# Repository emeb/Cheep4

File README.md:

# Cheep4

Yet another Eurorack digital oscillator

## Abstract

Cheep4 is a continuation of a series of low-spec / low-cost digital oscillator modules for Eurorack whose primary purpose is to demonstrate using extreme low-end microcontrollers to do DSP. The series includes the following earlier modules:

[cheep_mod](https://github.com/emeb/Old_Website/tree/main/synth/cheep_mod) - the original stripped-down done with an STM32F030 and a SPI DAC.

[cheep2](https://github.com/emeb/Old_Website/tree/main/synth/cheep2) - 2nd generation uses an STM32F031 and a stereo I2S DAC.

[cheep3a](https://github.com/emeb/cheep3a) - 3rd generation based on a CH32V003 and stereo I2S DAC faked out with a SPI interface.

Cheep4 dials up the functionality with a more advanced MCU - the STM32C542CCT6 which although more powerful is still inexpensive (under $2) - and a decent quality I2S DAC, as well as a more complete set of controls for the 1V/Octave input (Coarse, Fine, FM pots). Similar to the cheep3a, it has a button & LED mode select interface which provides seven distinct algorithms and nonvolatile memory to save the mode across power cycles. Behind the panel there are also USB and Qwiic connectors for upgrades and expansion.

## Features

- [STM32C542CC](https://www.st.com/en/microcontrollers-microprocessors/stm32c542cc.html) MCU with
  
  - Arm Cortex M33 at 144MHz
  
  - 256kB Flash
  
  - 64kB SRAM
  
  - CORDIC math coprocessor

- [PCM5100A](https://www.ti.com/product/PCM5100A) I2S DAC

- [GD25Q32](https://www.gigadevice.com/product/flash/spi-nor-flash/gd25q32c)  4MB SPI flash memory

- USB port

- [Qwiic](https://www.sparkfun.com/qwiic) I2C port

- 16-pin shrouded Eurorack power connector with +/-12V only

- 6x 9mm potentiometers
  
  - Coarse pitch
  
  - Fine pitch
  
  - FM pitch attenuator
  
  - CV1, CV2, CV3 offsets

- 8x 3.5mm mono jacks
  
  - 1V/Oct pitch input (+/-5V range)
  
  - FM pitch input
  
  - CV1, CV2, CV3 inputs (+/-5V range)
  
  - Sync input (digital, 0.7V threshold)
  
  - 2 +/-5V outputs

- Button + RGB LED for mode selection.

## Firmware

Firmware included with this project includes test code for all the critical MCU features as well as functional oscillator applications. All code is built with my own simplified make-based system and needs only an Arm GCC compiler and an ST-Link programmer. Code is based on the ST HAL2 hardware interface library as well as the Arm CMSIS low-level drivers and register definitions, both of which are included in this repository.

### Prerequisites

- [Arm GCC compiler](https://developer.arm.com/downloads/-/arm-gnu-toolchain-downloads)

- [ST-Link programmer](https://www.st.com/en/development-tools/hardware-debugger-and-programmer-tools-for-stm32/products.html) hardware interface - currently the only low-cost programmer/debugger that interfaces to the STM32C5 family MCUs.

- [STM32 Cube Programmer]([https://www.st.com/en/development-tools/stm32cubeprog.html) application installed - needed for interfacing to ST-Link programmer hardware. 

### Building

Change directories into the desired subdirectory and run `make` - this may require editing the Makefile to point to the installation locations of you prerequisites.

## Hardware

Kicad 9.0.x design files are included for both the passive front panel and active back panel. A Libreoffice ODS spreadsheet of the Bill of Materials (BOM) is available, or you can generate your own desired format from Kicad. No special assembly techniques are required beyond basic SMT and thru-hole soldering. Documentation includes:

- [Schematic (PDF format)](./doc/cheep4_sch.pdf)

- [Bill of Materials (ODS format)](Hardware/cheep4/cheep4_bom.ods)

## Lessons Learned

This project involved a fair bit of new material for me - not only is the STM32C542 a new family of MCU, but ST has chosen to migrate to a new HAL2 API for interfacing to their hardware, as well as a newer CubeMX2 configuration & code generation application. What follows are some notes on the new hardware, firmware and software experiences.

### STM32C542CCT6 Microcontroller

This device is a new low-cost part with a decent complement of peripherals and memory. The specific part chosen here is in a 48-pin LQFP which is just enough for all the interfaces needed on this oscillator project, including some diagnostic test pads, but there are larger (and smaller) pincount packages available. Overall the device doesn't feel significantly different from earlier offerings from STM, but there are some slight differences worth calling out:

##### Cortex M33 CPU

This type of CPU has been appearing in more and more devices lately, edging out the older Cortex M3, M4 and M7 cores that were common in the STM32 line. The main difference is support for secure boot which is critical for some applications but of no great interest to me.

##### Clock Generation

In the past most STM32 microcontrollers were outfitted with crystal oscillators, RC oscillators and PLLs that could synthesize a wide range of system clock frequencies from these sources. The STM32C5 family still supports crystal and RC oscillators but replaces the older more flexible PLLs with new "Programmable Speed Internal" sources which appear to be phase-locked oscillators with a very limited selection of reference and output frequencies. They still provide accurate and clean clock signals when properly configured, but cannot support fine resolution in selection of system clocks and generate only 100, 144 and 160MHz outputs (and some integer divisions of these).

##### EEPROM Emulation

The C5 family includes a new "User Data" region of flash memory which is addressed and managed separately from the typical program flash that's been a staple of previous STM32 parts. The User Data region has smaller sector sizes, more error correction bits and finer granularity when writing which allows more effective implementation of EEPROM data storage.

##### CORDIC coprocessor

First introduced in the STM32G4 series parts, this function allows fast and accurate computation of trigonometric and hyperbolic math functions without use of the main CPU. It's a very handy thing to have when doing DSP and audio applications and a welcome feature in a low-end "value" device.

##### Common Peripherals

The C5 family also has the usual assortment of SPI, I2C, I2S, CAN, UART, ADC, DAC and other peripherals. For the most part they are very similar to the same functions in earlier STM32 parts with minor variations as are typical across families.

##### Board design

At the package pin interface the C5 parts will be very familiar to anyone who has designed with earlier STM32 parts. The pin arrangements follow the same general layout and electrical characteristics are also similar. A few notable differences are:

- The use of the BOOT0 pin which is A) disabled by default in the option bytes and must be explicitly enabled if the system bootloader is needed, and B) can now be repurposed as GPIO.

- There is no longer a separate VDDA supply pin for the analog subsection. There are however still Vref pins which should be driven with clean reference supplies for the ADC and DAC.

### STM32 CubeMX2 & HAL2

Alongside the C5 family of parts, ST has introduced a new configuration and code generation tool CubeMX2 and the associated HAL2 library of low-level and mid-level drivers.

###### CubeMX2

[STM32 CubeMX](https://community.st.com/t5/developer-news/introducing-stm32cubemx2-a-new-flavor-of-stm32cubemx-tool/ba-p/885793) is the hardware configuration tool that ST has provided for many years which is an essential part of bringing up a new hardware design because it helps accelerate the setup of all the hardware resources on STM32 parts. CubeMX2 fills the exact same role for the C5 family. It has a significantly different UI from the older CubeMX application but the changes aren't particularly confusing - if you know how to drive CubeMX then it won't take too much effort to learn CubeMX2. The main difference is in the structure of the generated code. CubeMX2 has a radically different project architecture, with initialization code for every MCU subsystem broken out into separate files that are hierarchically separate from the user application code.

##### HAL2

The original HAL (Hardware Abstraction Library) was the follow up to ST's earlier Standard Peripheral Library, both of which encapsulated the necessary driver code for initializing and using the peripherals on every STM32 MCU. [HAL2](https://dev.st.com/stm32cube-docs/embedded-software/2.0.0/en/architecture/hal2-architecture.html) is similar to HAL and provides most of the same resources, but is sufficiently different in details that code written for HAL on older devices will not port without some effort - many of the function calls have changed in name and parameters so some careful study of the HAL2 source will be needed to ensure that ported code operates as required. 

There are some significant improvements in HAL2 however - primarily in build-time settings to optimize resource usage. Every peripheral subsystem can be configured to enable or disable features such as assertion, debuggin, DMA, etc. as required in the target application. HAL2 seems to produce tighter firmware and the API enables fairly straightforward user code that appears sturcturally simple and is fairly easy to optimize.

### Cheep4 Application

In the specific application to a low-cost Eurorack digital oscillator, the STM32C542 features were used as follows:

##### Clocking

By default at startup the STM32C542 runs at full speed from the 144MHz HSI RC oscillator. This source is not highly accurate and exhibits a fair amount of phase noise as shown in the figure below:

After bootup, a 24MHz HSE crystal is used as reference to the PSIS generating a very clean and accurate 144MHz system clock as seen in this screenshot:

##### ADC for CV input

The C542 ADC performed very well for control voltage conversions. Driver code was based on the init code generated by CubeMX2, combined with calibration and startup functions inferred by reading examples and the documentation in the HAL2 driver. Converted data appears to be extremely clean and stable, with very little noise in the least-significant bits.

##### I2S for audio output

The C542 includes two SPI ports that also support full-duplex I2S for audio applications. Port SPI2 is configured to drive the PCM5100A audio DAC via TX-only I2S with 16-bit stereo output at a sample rate of 95744Hz - the closest rate to 96kHz available using the on-chip clocking resources. Initialization and operation via the HAL2 API was straightforward and optimization via bypassing the ISR callbacks provided a modest reduction in CPU resources used.

##### DAC for audio output

Although the Cheep4 board doesn't explicitly support use of the C542 on-chip DACs for its audio output channels, the DAC outputs are available on testpoints and could conceivably be wired into the output buffer with appropriate gain and offset changes. Driver code for the DACs has been evaluated and appears to work as expected, achieving the same stereo @ 95744Hz sample rate as was used in the I2S case. The configuration requires using one of the available timer peripherals to generate a sample-rate trigger signal to the two DAC channels, coupled to DMA driving the dual left-justified data register with 32-bit words containing two 16-bit signed data samples.

##### SPI for external flash

An external GD25Q32 4MB SPI flash chip is interfaced via port SPI1 for storage of audio samples or wavetables. XIP or memory mapped access is not available so reading and writing is handled exclusively via indirect mode. Althought this flash device supports SPI clocks in excess of 80MHz, most reliable operation was seen with a SPI prescaler of 4 yielding a clock rate of 36MHz.

##### Timer input capture for sync

A common feature found in audio oscillators is "sync" which allows resetting the phase of the oscillator to a known point to synchronize it to an external source. The Cheep4 system generates 4 stereo samples per DMA IRQ buffer period and checking for sync once per period would result in poor timing resolution that contributes to harsh aliasing distortion. By sampling the sync input with a timer at the sample rate it's possible to improve the timing resolution and reduce the aliasing distortion significantly. Timer 12 clocked at 4x the sample rate with falling-edge input capture provides a high-resolution indicator of exactly which buffer sample to apply the phase reset.

##### Button and LED user interface

An RGB LED can provide up to seven unique colors without requiring PWM for fine color resolution which would introduce supply current spikes that could contaminate the audio outputs. A single front-panel tactile pushbutton is sampled at the 1ms Systick rate, debounced and the rising edge is used to advance the LED color and audio mode. In addition to the front-panel button, the BOOT0 button on the back of the PCB is also sampled and debounced and is available for future use.

##### EEPROM emulation

The on-chip flash "User Data" region is configured in its default 48kB mode with 1.5kB/sector and the last sector in Bank2 is used to store 768 16-bit half-words. Each word consists of 15 bits of user data and an empty bit. Emulation code allows storing just 15 bits of state information and every time the state is updated a new half-word of the total 768 is used. When all locations are used the whole sector is erased and the process restarts, thus wear-leveling and multiplying the nominal 10k write endurance to over 7 million cycles.

##### I2C for Qwiic connection

A standard Qwiic connection is provided which is driven by port I2C1 at the standard 100kHz rate. This can be used for expansion of the user interface with more buttons, LEDs and even OLED displays. An inexpensive SSD1306 128x64 OLED display driver has been tested on this interface.

##### USB Full Speed Device

The C542 includes a full-speed (12Mbps) device/host port which has been configured as device-only on the Cheep4 board. It has been confirmed to work in the System bootloader USB DFU mode and may be used in the future for a UF2-based firmware update and/or wavetable loader for the external SPI flash.

##### Debug / Log port

SWD programming / debugging and USART1 logging are provided on an ST / ARM standard 14-pin 0.127mm connector. Additionally four GPIO testpoints are provided for diagnostic signalling, including timers, clock outputs and DAC voltages.

## PCB Design notes

The V0.1 PCB design has a few issues that should be corrected if ever updated:

- Some 0402 footprints crept in due to copy/paste from other board designs. These should be converted to 0603.

- Provide option to bypass the PCM5100A audio DAC and allow the STM32C542 on-chip dual 12-bit DAC to be used instead. This would entail adding DNI resistors for the -5V reference voltage to center the 0-3.3V DAC outputs on 0V, as well as solderblob jumpers to select either MCU DAC or PCM5100A outputs.

- Add testpoints on the currently unconnected PC14/15 pins for additional diagnostics or connection of a 32kHz crystal.

- Consider an SMPS regulator to efficiently reduce the Eurorack +12V to +5V instead of the LDO used on V0.1.

- Consider TVS diode protection on the USB device port.

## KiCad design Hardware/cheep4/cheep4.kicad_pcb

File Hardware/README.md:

# Cheep4 Hardware

This directory contains the KiCAD design files for the Cheep4 module, including both the passive front panel and the electrical rear panel.

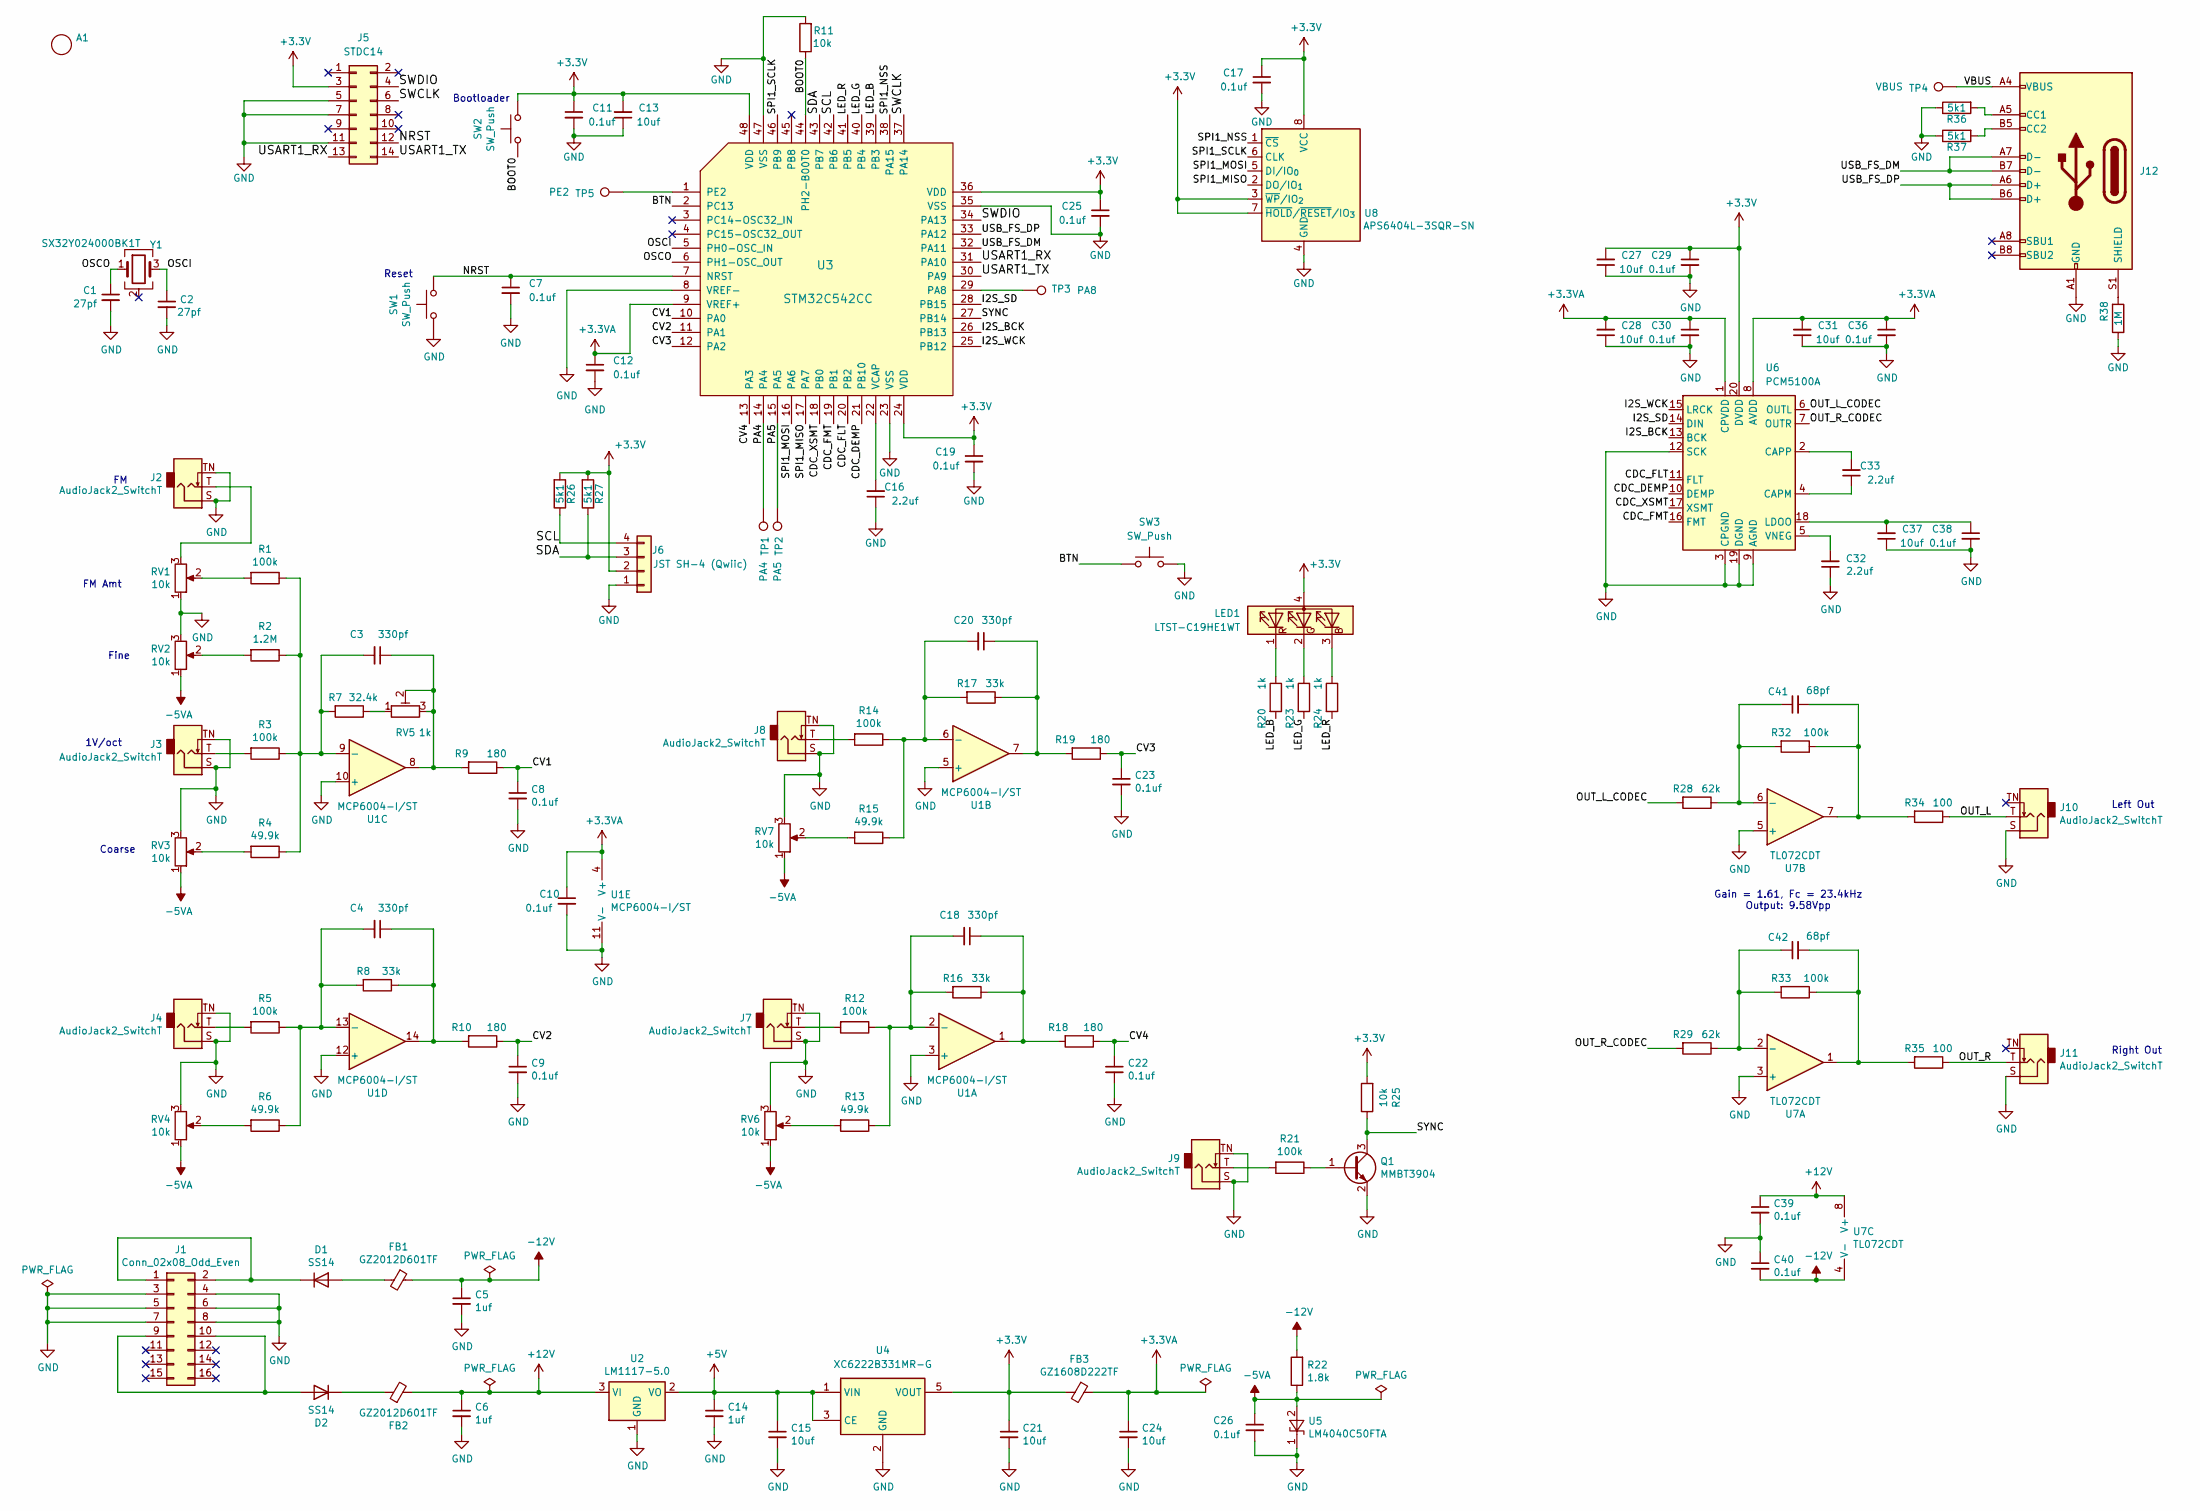
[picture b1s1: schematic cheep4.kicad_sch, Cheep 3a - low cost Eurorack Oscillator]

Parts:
A1: avatar_small
C1, C2: 27pf; C_0603_1608Metric
C3, C4, C18, C20: 330pf; C_0603_1608Metric
C5, C6, C14: 1uf; C_0603_1608Metric
C7, C8, C9, C10, C11, C12, C17, C19, C22, C23, C25, C26, C29, C30, C36, C38, C39, C40: 0.1uf; C_0603_1608Metric
C13, C15, C21, C24, C27, C28, C31, C37: 10uf; C_0805_2012Metric
C16, C32, C33: 2.2uf; C_0805_2012Metric
C41, C42: 68pf; C_0603_1608Metric
D1, D2: SS14; D_SMA
FB1, FB2: GZ2012D601TF; L_0805_2012Metric
FB3: GZ1608D222TF; L_0603_1608Metric
J1: Conn_02x08_Odd_Even; con16_2X8_S4_TEC
J2, J3, J4, J7, J8, J9, J10, J11: AudioJack2_SwitchT; Jack_3.5mm_QingPu_WQP-PJ398SM_Vertical_CircularHoles
J5: STDC14; PinHeader_2x07_P1.27mm_Vertical
J6: JST SH-4 (Qwiic); JST_SH_SM04B-SRSS-TB_04x1.00mm_Angled
J12: USB_C_Receptacle_USB2.0; USB_C_Receptacle_HRO_TYPE-C-31-M-12
LED1: LTST-C19HE1WT; LED_LiteOn_LTST-C19HE1WT
Q1: MMBT3904; SOT-23
R1, R3, R5, R12, R14, R21, R32, R33: 100k; R_0603_1608Metric
R2: 1.2M; R_0603_1608Metric
R4, R6, R13, R15: 49.9k; R_0603_1608Metric
R7: 32.4k; R_0603_1608Metric
R8, R16, R17: 33k; R_0603_1608Metric
R9, R10, R18, R19: 180; R_0603_1608Metric
R11: 10k; R_0402_1005Metric
R20, R23, R24: 1k; R_0603_1608Metric
R22: 1.8k; R_0603_1608Metric
R25: 10k; R_0603_1608Metric
R26, R27, R36, R37: 5k1; R_0402_1005Metric
R28, R29: 62k; R_0603_1608Metric
R34, R35: 100; R_0603_1608Metric
R38: 1M; R_0402_1005Metric
RV1, RV2, RV3, RV4, RV6, RV7: 10k; Potentiometer_TT_P0915N
RV5: 1k; 23BR500LFTR
SW1, SW2: SW_Push; SW_Push_1P1T_NO_CK_KMR2
SW3: SW_Push; SW_PUSH_6mm
TP1: PA4; TestPoint_Pad_D1.0mm
TP2: PA5; TestPoint_Pad_D1.0mm
TP3: PA8; TestPoint_Pad_D1.0mm
TP4: VBUS; TestPoint_Pad_D1.0mm
TP5: PE2; TestPoint_Pad_D1.0mm
U1: MCP6004-I/ST; TSSOP-14_4.4x5mm_P0.65mm
U2: LM1117-5.0; SOT-223-3_TabPin2
U3: STM32C542CC; LQFP-48_7x7mm_P0.5mm
U4: XC6222B331MR-G; SOT-23-5
U5: LM4040C50FTA; SOT-23
U6: PCM5100A; TSSOP-20_4.4x6.5mm_P0.65mm
U7: TL072CDT; SOIC-8_3.9x4.9mm_P1.27mm
U8: APS6404L-3SQR-SN; SOIC-8_3.9x4.9mm_P1.27mm
Y1: SX32Y024000BK1T; Crystal_SMD_3225-4Pin_3.2x2.5mm

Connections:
+3.3V: C11.1, C13.2, C17.1, C19.1, C21.1, C25.1, C27.2, C29.1, FB3.2, J5.3, J6.2, LED1.4 (A), R25.2, R26.2, R27.2, SW2.1, U3.24 (VDD), U3.36 (VDD), U3.48 (VDD), U4.5 (VOUT), U6.20 (DVDD), U8.3 (~WP/IO_{2}), U8.7 (~HOLD/~RESET/IO_{3}), U8.8 (VCC)
+3.3VA: C10.1, C12.1, C24.1, C28.2, C30.1, C31.2, C36.1, FB3.1, U1.4 (V+), U3.9 (VREF+), U6.1 (CPVDD), U6.8 (AVDD)
+5V: C14.1, C15.1, U2.2 (VO), U4.1 (VIN), U4.3 (CE)
+12V: C6.1, C39.1, FB2.2, U2.3 (VI), U7.8 (V+)
-5VA: C26.1, R22.1, RV2.1, RV3.1, RV4.1, RV6.1, RV7.1, U5.2 (A)
-12V: C5.1, C40.2, FB1.1, R22.2, U7.4 (V-)
/BOOT0: R11.1, SW2.2, U3.44 (PH2-B00T0)
/BTN: SW3.1, U3.2 (PC13)
/CDC_DEMP: U3.21 (PB10), U6.10 (DEMP)
/CDC_FLT: U3.20 (PB2), U6.11 (FLT)
/CDC_FMT: U3.19 (PB1), U6.16 (FMT)
/CDC_XSMT: U3.18 (PB0), U6.17 (XSMT)
/CV1: C8.1, R9.1, U3.10 (PA0)
/CV2: C9.1, R10.1, U3.11 (PA1)
/CV3: C23.1, R19.1, U3.12 (PA2)
/CV4: C22.1, R18.1, U3.13 (PA3)
/I2S_BCK: U3.26 (PB13), U6.13 (BCK)
/I2S_SD: U3.28 (PB15), U6.14 (DIN)
/I2S_WCK: U3.25 (PB12), U6.15 (LRCK)
/LED_B: R20.2, U3.39 (PB3)
/LED_G: R23.2, U3.40 (PB4)
/LED_R: R24.2, U3.41 (PB5)
/NRST: C7.1, J5.12, SW1.1, U3.7 (NRST)
/OSCI: C2.1, U3.5 (PH0-OSC_IN), Y1.3
/OSCO: C1.1, U3.6 (PH1-OSC_OUT), Y1.1
/OUT_L: J10.T, R34.1
/OUT_L_CODEC: R28.2, U6.6 (OUTL)
/OUT_R: J11.T, R35.1
/OUT_R_CODEC: R29.2, U6.7 (OUTR)
/PA4: TP1.1, U3.14 (PA4)
/PA5: TP2.1, U3.15 (PA5)
/SCL: J6.4, R26.1, U3.42 (PB6)
/SDA: J6.3, R27.1, U3.43 (PB7)
/SPI1_MISO: U3.17 (PA7), U8.2 (DO/IO_{1})
/SPI1_MOSI: U3.16 (PA6), U8.5 (DI/IO_{0})
/SPI1_NSS: U3.38 (PA15), U8.1 (~CS)
/SPI1_SCLK: U3.46 (PB9), U8.6 (CLK)
/SWCLK: J5.6, U3.37 (PA14)
/SWDIO: J5.4, U3.34 (PA13)
/SYNC: Q1.3 (C), R25.1, U3.27 (PB14)
/USART1_RX: J5.13, U3.31 (PA10)
/USART1_TX: J5.14, U3.30 (PA9)
/USB_FS_DM: J12.A7 (D-), J12.B7 (D-), U3.32 (PA11)
/USB_FS_DP: J12.A6 (D+), J12.B6 (D+), U3.33 (PA12)
/VBUS: J12.A4 (VBUS), J12.A9 (VBUS), J12.B4 (VBUS), J12.B9 (VBUS), TP4.1
GND: C1.2, C2.2, C5.2, C6.2, C7.2, C8.2, C9.2, C10.2, C11.2, C12.2, C13.1, C14.2, C15.2, C16.1, C17.2, C19.2, C21.2, C22.2, C23.2, C24.2, C25.2, C26.2, C27.1, C28.1, C29.2, C30.2, C31.1, C32.1, C36.2, C37.1, C38.2, C39.2, C40.1, J1.3, J1.4, J1.5, J1.6, J1.7, J1.8, J2.S, J2.TN, J3.S, J3.TN, J4.S, J4.TN, J5.5, J5.7, J5.11, J6.1, J7.S, J7.TN, J8.S, J8.TN, J9.S, J9.TN, J10.S, J11.S, J12.A1 (GND), J12.A12 (GND), J12.B1 (GND), J12.B12 (GND), Q1.2 (E), R11.2, R36.1, R37.1, R38.1, RV1.1, RV2.3, RV3.3, RV4.3, RV6.3, RV7.3, SW1.2, SW3.2, U1.3 (+), U1.5 (+), U1.10 (+), U1.11 (V-), U1.12 (+), U2.1 (GND)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
unnamed: C3.1, R9.2, RV5.2, RV5.3, U1.8
unnamed: C4.1, R8.1, R10.2, U1.14
unnamed: C18.1, R16.1, R18.2, U1.1
unnamed: C20.1, R17.1, R19.2, U1.7
unnamed: C41.2, R32.1, R34.2, U7.7
unnamed: C42.2, R33.1, R35.2, U7.1
unnamed: D1.2 (A), FB1.2
unnamed: D1.1 (K), J1.1, J1.2
unnamed: D2.2 (A), J1.9, J1.10
unnamed: D2.1 (K), FB2.1
unnamed: J2.T, RV1.3
unnamed: J3.T, R3.2
unnamed: J4.T, R5.2
unnamed: J7.T, R12.2
unnamed: J8.T, R14.2
unnamed: J9.T, R21.2
unnamed: J12.A5 (CC1), R36.2
unnamed: J12.B5 (CC2), R37.2
unnamed: J12.S1 (SHIELD), R38.2
unnamed: LED1.3 (BK), R24.1
unnamed: LED1.2 (GK), R23.1
unnamed: LED1.1 (RK), R20.1
unnamed: Q1.1 (B), R21.1
unnamed: R1.2, RV1.2
unnamed: R2.2, RV2.2
unnamed: R4.2, RV3.2
unnamed: R6.2, RV4.2
unnamed: R7.1, RV5.1
unnamed: R13.2, RV6.2
unnamed: R15.2, RV7.2
unnamed: C18.2, R12.1, R13.1, R16.2, U1.2 (-)
unnamed: C20.2, R14.1, R15.1, R17.2, U1.6 (-)
unnamed: C3.2, R1.1, R2.1, R3.1, R4.1, R7.2, U1.9 (-)
unnamed: C4.2, R5.1, R6.1, R8.2, U1.13 (-)
unnamed: TP3.1, U3.29 (PA8)
unnamed: TP5.1, U3.1 (PE2)
unnamed: C16.2, U3.22 (VCAP)
unnamed: C33.1, U6.4 (CAPM)
unnamed: C33.2, U6.2 (CAPP)
unnamed: C37.2, C38.1, U6.18 (LDOO)
unnamed: C32.2, U6.5 (VNEG)
unnamed: C42.1, R29.1, R33.2, U7.2 (-)
unnamed: C41.1, R28.1, R32.2, U7.6 (-)

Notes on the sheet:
Reset
Gain = 1.61, Fc = 23.4kHz Output: 9.58Vpp
Coarse
FM Amt
Bootloader
Right Out
1V/oct
Left Out
Fine

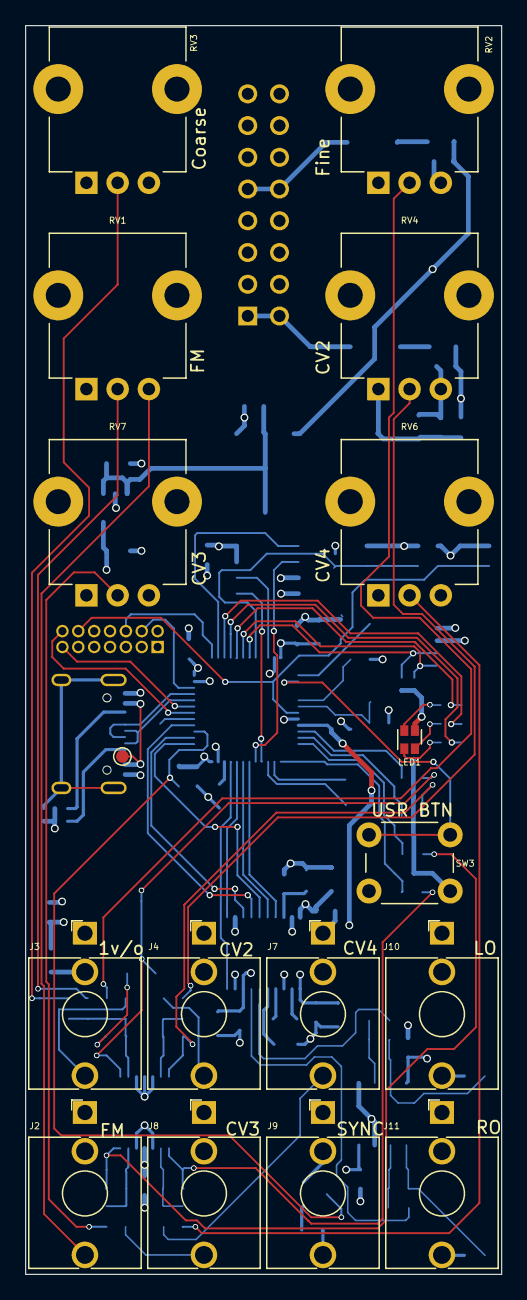
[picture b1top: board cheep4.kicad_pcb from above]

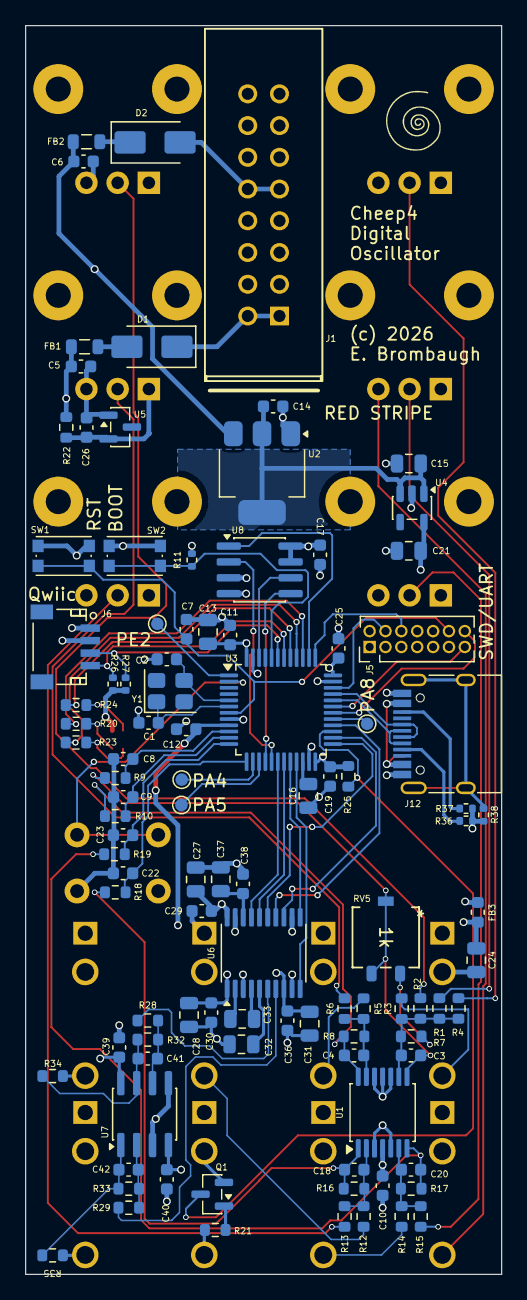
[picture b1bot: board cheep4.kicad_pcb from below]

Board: 4 copper layers, 38.1 x 100.0 mm, 120 parts (103 on the bottom side), 89 nets.

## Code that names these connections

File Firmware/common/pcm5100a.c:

/*
 * pcm5100a.c - Cheep4 PCM5100A I2S DAC setup
 * 04-14-26 E. Brombaugh
 */

#include "pcm5100a.h"

#define XSMT_PIN	HAL_GPIO_PIN_0
#define FMT_PIN		HAL_GPIO_PIN_1
#define FLT_PIN		HAL_GPIO_PIN_2
#define DEMP_PIN	HAL_GPIO_PIN_10

/*
 * Initialize the nucleo LEDs
 */
hal_status_t PCM5100A_Init(void)
{
  hal_gpio_config_t  gpio_config;

  HAL_RCC_GPIOB_EnableClock();

  /*
    GPIO pin labels :
    PB3   ---------> LED_B
    PB4   ---------> LED_G
    PB5   ---------> LED_R
    */
  /* Configure PB0,1,2,10 GPIO pins in output mode */
  gpio_config.mode            = HAL_GPIO_MODE_OUTPUT;
  gpio_config.speed           = HAL_GPIO_SPEED_FREQ_LOW;
  gpio_config.pull            = HAL_GPIO_PULL_NO;
  gpio_config.output_type     = HAL_GPIO_OUTPUT_PUSHPULL;
  gpio_config.init_state      = HAL_GPIO_PIN_RESET;
  if(HAL_GPIO_Init(HAL_GPIOB, XSMT_PIN | FMT_PIN | FLT_PIN | DEMP_PIN, &gpio_config) != HAL_OK)
  {
    return HAL_ERROR;
  }

  return HAL_OK;
}

/*
 * Set DAC config
 */
void PCM5100A_Set(uint8_t cfg)
{
	if(cfg & CDC_XSMT)
		GPIOB->BSRR = XSMT_PIN;
	else
		GPIOB->BSRR = XSMT_PIN<<16;
	
	if(cfg & CDC_FMT)
		GPIOB->BSRR = FMT_PIN;
	else
		GPIOB->BSRR = FMT_PIN<<16;
	
	if(cfg & CDC_FLT)
		GPIOB->BSRR = FLT_PIN;
	else
		GPIOB->BSRR = FLT_PIN<<16;
	
	if(cfg & CDC_DEMP)
		GPIOB->BSRR = DEMP_PIN;
	else
		GPIOB->BSRR = DEMP_PIN<<16;
}

/*
 * Get DAC config
 */
uint8_t PCM5100A_Get(void)
{
	uint8_t result = 0;
	
	if(GPIOB->ODR & XSMT_PIN)
		result |= CDC_XSMT;
	
	if(GPIOB->ODR & FMT_PIN)
		result |= CDC_FMT;
	
	if(GPIOB->ODR & FLT_PIN)
		result |= CDC_FLT;
	
	if(GPIOB->ODR & DEMP_PIN)
		result |= CDC_DEMP;
	
	return result;
}

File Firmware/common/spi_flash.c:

/*
 * spi_flash.c - Cheep4 SPI Flash driver
 * 04-15-26 E. Brombaugh
 */

#include "spi_flash.h"
#include "printf.h"

/* select software or hardware CS control - uncomment for HW */
//#define CS_HW

/* macros for toggling the CS line - do we need them? */
#ifdef CS_HW
#define SPI_FLASH_CS_LOW()
#define SPI_FLASH_CS_HIGH()
#else
#define SPI_FLASH_CS_LOW()	(GPIOA->BSRR = HAL_GPIO_PIN_15<<16)
#define SPI_FLASH_CS_HIGH()	(GPIOA->BSRR = HAL_GPIO_PIN_15)
#endif

static hal_spi_handle_t hSPI1;

/*
 * Initialize the SPI port
 */
hal_status_t SPI_Flash_Init(void)
{
	hal_spi_config_t spi_config;

	if(HAL_SPI_Init(&hSPI1, HAL_SPI1) != HAL_OK)
	{
		return HAL_ERROR;
	}

	HAL_RCC_SPI1_EnableClock();

	if(HAL_RCC_SPI1_SetKernelClkSource(HAL_RCC_SPI1_CLK_SRC_PCLK2) != HAL_OK)
	{
		return HAL_ERROR;
	}

	spi_config.mode = HAL_SPI_MODE_MASTER;
	spi_config.direction = HAL_SPI_DIRECTION_FULL_DUPLEX;
	spi_config.data_width = HAL_SPI_DATA_WIDTH_8_BIT;
	spi_config.clock_polarity = HAL_SPI_CLOCK_POLARITY_LOW;
	spi_config.clock_phase = HAL_SPI_CLOCK_PHASE_1_EDGE;
	spi_config.baud_rate_prescaler = HAL_SPI_BAUD_RATE_PRESCALER_4;
	spi_config.first_bit = HAL_SPI_MSB_FIRST;
#ifdef CS_HW
	spi_config.nss_pin_management = HAL_SPI_NSS_PIN_MGMT_OUTPUT;
#else
	spi_config.nss_pin_management = HAL_SPI_NSS_PIN_MGMT_INTERNAL;
#endif

	if(HAL_SPI_SetConfig(&hSPI1, &spi_config) != HAL_OK)
	{
		return HAL_ERROR;
	}

#ifdef CS_HW
	hal_spi_nss_config_t spi_nss_config;

	spi_nss_config.nss_pulse = HAL_SPI_NSS_PULSE_DISABLE;
	spi_nss_config.nss_polarity = HAL_SPI_NSS_POLARITY_LOW;
	spi_nss_config.nss_mssi_delay = HAL_SPI_NSS_MSSI_DELAY_0_CYCLE;

	if(HAL_SPI_SetConfigNSS(&hSPI1, &spi_nss_config) != HAL_OK)
	{
		return HAL_ERROR;
	}
#endif
	
	if(HAL_SPI_EnableMosiMisoSwap(&hSPI1) != HAL_OK)
	{
		return HAL_ERROR;
	}

	HAL_RCC_GPIOB_EnableClock();

	HAL_RCC_GPIOA_EnableClock();

	hal_gpio_config_t  gpio_config;

	/**
	SPI1 GPIO Configuration

	[GPIO Pin] ------> [Signal Name]

	   PB9     ------>   SPI1_SCK
	**/
	gpio_config.mode        = HAL_GPIO_MODE_ALTERNATE;
	gpio_config.output_type = HAL_GPIO_OUTPUT_PUSHPULL;
	gpio_config.pull        = HAL_GPIO_PULL_NO;
	gpio_config.speed       = HAL_GPIO_SPEED_FREQ_HIGH;
	gpio_config.alternate   = HAL_GPIO_AF_6;
	HAL_GPIO_Init(HAL_GPIOB, HAL_GPIO_PIN_9, &gpio_config);

	/**
	SPI1 GPIO Configuration

	[GPIO Pin] ------> [Signal Name]

	   PA6     ------>   SPI1_MISO
	   PA7     ------>   SPI1_MOSI
	**/
	gpio_config.mode        = HAL_GPIO_MODE_ALTERNATE;
	gpio_config.output_type = HAL_GPIO_OUTPUT_PUSHPULL;
	gpio_config.pull        = HAL_GPIO_PULL_NO;
	gpio_config.speed       = HAL_GPIO_SPEED_FREQ_HIGH;
	gpio_config.alternate   = HAL_GPIO_AF_5;
	HAL_GPIO_Init(HAL_GPIOA, HAL_GPIO_PIN_6 | HAL_GPIO_PIN_7, &gpio_config);

	/**
	SPI1 GPIO Configuration

	[GPIO Pin] ------> [Signal Name]

	   PA15    ------>   SPI1_NSS
	**/
#ifdef CS_HW
	/* hardware control */
	gpio_config.mode        = HAL_GPIO_MODE_ALTERNATE;
	gpio_config.output_type = HAL_GPIO_OUTPUT_PUSHPULL;
	gpio_config.pull        = HAL_GPIO_PULL_UP;
	gpio_config.speed       = HAL_GPIO_SPEED_FREQ_HIGH;
	gpio_config.alternate   = HAL_GPIO_AF_5;
	HAL_GPIO_Init(HAL_GPIOA, HAL_GPIO_PIN_15, &gpio_config);
#else
	/* software control */
	gpio_config.mode        = HAL_GPIO_MODE_OUTPUT;
	gpio_config.output_type = HAL_GPIO_OUTPUT_PUSHPULL;
	gpio_config.pull        = HAL_GPIO_PULL_NO;
	gpio_config.speed       = HAL_GPIO_SPEED_FREQ_HIGH;
	gpio_config.init_state  = HAL_GPIO_PIN_RESET;
	HAL_GPIO_Init(HAL_GPIOA, HAL_GPIO_PIN_15, &gpio_config);
#endif

#if 0
	printf("SPI_Flash_Init() - Diag toggle CS\n\r");
	while(1)
	{
		SPI_FLASH_CS_LOW();
		HAL_Delay(1);
		SPI_FLASH_CS_HIGH();
		HAL_Delay(2);
	}
#endif
	
	return HAL_OK;
}

/*
 * Read a buffer of SFDP info
 */
uint32_t SPI_Flash_ReadSFDP(uint32_t ReadAddr, uint8_t *Data, uint32_t sz)
{	
	/* assert CS */
	SPI_FLASH_CS_LOW();

	/* build command header */
	uint8_t tx[] = 
	{
		0x5a,
		(ReadAddr>>16)&0xff,
		(ReadAddr>>8)&0xff,
		ReadAddr&0xff,
		0x00
	};
	HAL_SPI_Transmit(&hSPI1, tx, sizeof(tx), 10);
	
	/* receive SFDP data */
	HAL_SPI_Receive(&hSPI1, Data, sz, 10);
	
	/* de-assert CS */
	SPI_FLASH_CS_HIGH();
    
    return 0;
}

/*
 * Read a buffer of bytes
 */
uint32_t SPI_Flash_ReadBuff(uint32_t ReadAddr, uint8_t *Data, uint32_t sz)
{	
	/* assert CS */
	SPI_FLASH_CS_LOW();
	/* build command header */
	uint8_t tx[] = 
	{
		0x03,	// SPI read
		(ReadAddr>>16)&0xff,
		(ReadAddr>>8)&0xff,
		ReadAddr&0xff,
	};
	HAL_SPI_Transmit(&hSPI1, tx, sizeof(tx), 10);
	
	/* receive SFDP data */
	HAL_SPI_Receive(&hSPI1, Data, sz, 10);

	/* de-assert CS */
	SPI_FLASH_CS_HIGH();
    
    return 0;
}

/*
 * Write Enable
 */
void SPI_Flash_WREN(void)
{    
    /* assert CS */
    SPI_FLASH_CS_LOW();
	
	/* Set WREN bit */
	uint8_t cmd = 0x06;
	HAL_SPI_Transmit(&hSPI1, &cmd, 1, 10);

    /* de-assert CS */
    SPI_FLASH_CS_HIGH();
}

/*
 * Unlock after powerup
 */
void SPI_Flash_GobalUnlock(void)
{    
    /* write enable */
    SPI_Flash_WREN();

    /* assert CS */
    SPI_FLASH_CS_LOW();
	
	/* Set Global Unlock bit */
	uint8_t cmd = 0x98;
	HAL_SPI_Transmit(&hSPI1, &cmd, 1, 10);
	
    /* de-assert CS */
    SPI_FLASH_CS_HIGH();
}

/*
 * Poll Status
 */
uint8_t SPI_Flash_PollStatus(void)
{
    uint8_t status;
    
    /* assert CS */
    SPI_FLASH_CS_LOW();
	
	/* Get status from flash */
	uint8_t cmd = 0x05;
	HAL_SPI_Transmit(&hSPI1, &cmd, 1, 10);
	HAL_SPI_Receive(&hSPI1, &status, 1, 10);

    /* de-assert CS */
    SPI_FLASH_CS_HIGH();
    
    return status;
}

/*
 * Erase Sectors
 */
uint32_t SPI_Flash_EraseSectors(uint32_t SectAddr,  uint32_t sz)
{
    while(sz--)
    {
        /* write enable */
        SPI_Flash_WREN();

        /* assert CS */
        SPI_FLASH_CS_LOW();

		/* build command header for Erase */
		uint8_t tx[] = 
		{
			0x20,	// sector erase
			(SectAddr>>16)&0xff,
			(SectAddr>>8)&0xff,
			SectAddr&0xff,
		};
		HAL_SPI_Transmit(&hSPI1, tx, sizeof(tx), 10);
		
        /* de-assert CS */
        SPI_FLASH_CS_HIGH();
		
        /* poll status to wait for not busy */
        while(SPI_Flash_PollStatus() & 1)
        {
        }
        
        /* advance address one sector */
        SectAddr += 0x1000;
    }
    
    return 0;    
}

/*
 * Write a buffer of bytes
 */
uint32_t SPI_Flash_WriteBuff(uint32_t WriteAddr, uint8_t *Data, uint32_t sz)
{
    /* write enable */
    SPI_Flash_WREN();

    /* assert CS */
    SPI_FLASH_CS_LOW();
	
	/* build command header for page program */
	uint8_t tx[] = 
	{
		0x02,	// page program
		(WriteAddr>>16)&0xff,
		(WriteAddr>>8)&0xff,
		WriteAddr&0xff,
	};
	HAL_SPI_Transmit(&hSPI1, tx, sizeof(tx), 10);
	HAL_SPI_Transmit(&hSPI1, Data, sz, 10);	
	
    /* de-assert CS */
    SPI_FLASH_CS_HIGH();
    
    /* poll status to wait for not busy */
    while(SPI_Flash_PollStatus() & 1)
    {
    }
    
    return 0;
}

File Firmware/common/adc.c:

/*
 * adc.c - cheep4 STM32C542 adc setup
 * 04-12-2026 E. Brombaugh
 */

#include <string.h>
#include "adc.h"
#include "printf.h"

/* uncomment to shortcut HAL callbacks */
#define SHORTHAL

/* uncomment to enable IRQ diag on TP3 / PA8 pin */
//#define DIAG

#ifdef DIAG
#define DIAG_LOW()	(GPIOA->BSRR=(HAL_GPIO_PIN_8<<16))
#define DIAG_HIGH()	(GPIOA->BSRR=HAL_GPIO_PIN_8)
#else
#define DIAG_LOW()
#define DIAG_HIGH()
#endif

static hal_adc_handle_t hADC1;
static hal_dma_node_t DMA_Node_ADC1;
static hal_dma_handle_t hLPDMA1_CH0;

int16_t adc_buffer[ADC_BUFSZ], adc_proc_buffer[ADC_BUFSZ];

typedef enum
{
	ADC_RESET,
	ADC_RUNNING,
	ADC_PAUSED,
} adc_state_t;

static adc_state_t adc_state = ADC_RESET;

/*
 * ADC DMA TC callback
 */
void ADC_TC_Callback(hal_adc_handle_t *hADC)
{
#ifndef SHORTHAL
	/* grab data from previous DMA pass */
	memcpy(adc_proc_buffer, adc_buffer, ADC_BUFSZ*sizeof(int16_t));
#endif
}

/*
 * Initialize the breakout board LED
 */
hal_status_t ADC_Init(void)
{
	/* ADC_DAC prescaler is set to 36MHz in the RCC perif setup of mx.c */
	HAL_RCC_ADC12_EnableClock();

	if(HAL_RCC_ADCDAC_SetKernelClkSource(HAL_RCC_ADCDAC_CLK_SRC_HSIK) != HAL_OK)
	{
		return HAL_ERROR;
	}

	if(HAL_ADC_Init(&hADC1, HAL_ADC1) != HAL_OK)
	{
		return HAL_ERROR;
	}

	hal_adc_config_t adc_config;
	hal_adc_channel_config_t adc_channel_config;

	adc_config.resolution          = HAL_ADC_RESOLUTION_12_BIT;
	adc_config.sampling_mode       = HAL_ADC_SAMPLING_MODE_NORMAL;
	HAL_ADC_SetConfig(&hADC1, &adc_config);

	/****************************************************************************/
	/* Configuration of basic features (mandatory)                              */
	/****************************************************************************/

	/* ==================== Group Regular ====================*/
	hal_adc_reg_config_t reg_config;
	reg_config.trigger_src        = HAL_ADC_REG_TRIG_SOFTWARE;
	reg_config.sequencer_length   = ADC_BUFSZ;
	reg_config.sequencer_discont  = HAL_ADC_REG_SEQ_DISCONT_DISABLE;
	reg_config.continuous         = HAL_ADC_REG_CONV_CONTINUOUS;
	reg_config.overrun            = HAL_ADC_REG_OVR_DATA_OVERWRITTEN;
	HAL_ADC_REG_SetConfig(&hADC1, &reg_config);

	adc_channel_config.group           = HAL_ADC_GROUP_REGULAR;
	adc_channel_config.sequencer_rank  = 1;
	adc_channel_config.sampling_time   = HAL_ADC_SAMPLING_TIME_8CYCLES;
	adc_channel_config.input_mode      = HAL_ADC_IN_SINGLE_ENDED;
	HAL_ADC_SetConfigChannel(&hADC1, HAL_ADC_CHANNEL_0, &adc_channel_config);

	adc_channel_config.sequencer_rank  = 2;
	HAL_ADC_SetConfigChannel(&hADC1, HAL_ADC_CHANNEL_1, &adc_channel_config);

	adc_channel_config.sequencer_rank  = 3;
	HAL_ADC_SetConfigChannel(&hADC1, HAL_ADC_CHANNEL_2, &adc_channel_config);

	adc_channel_config.sequencer_rank  = 4;
	HAL_ADC_SetConfigChannel(&hADC1, HAL_ADC_CHANNEL_3, &adc_channel_config);

	/****************************************************************************/
	/* Configuration of additional features (optional)                          */
	/****************************************************************************/
	/* 16x OS -> roughly 27kSPS/chl for 4chl, 8cyc sample time, 36MHz clock */
	hal_adc_ovs_config_t ovs_config;
	ovs_config.scope = LL_ADC_OVS_REG_CONTINUED;
	ovs_config.discont = LL_ADC_OVS_CONT;
	ovs_config.ratio = 16;	// oversample by 16x
	ovs_config.shift = 4;	// divide by 16
	if(HAL_ADC_SetConfigOverSampling(&hADC1, HAL_ADC_OVS_1, &ovs_config) != HAL_OK)
	{
		return HAL_ERROR;
	}
	
	/****************************************************************************/
	/* Configuration of GPIO                          */
	/****************************************************************************/
	HAL_RCC_GPIOA_EnableClock();

	hal_gpio_config_t  gpio_config;

	/**
	ADC1 GPIO Configuration

	[GPIO Pin] ------> [Signal Name]

	   PA0     ------>   ADC1_IN0
	   PA1     ------>   ADC1_IN1
	   PA2     ------>   ADC1_IN2
	   PA3     ------>   ADC1_IN3
	**/
	gpio_config.mode        = HAL_GPIO_MODE_ANALOG;
	gpio_config.pull        = HAL_GPIO_PULL_NO;
	HAL_GPIO_Init(HAL_GPIOA, HAL_GPIO_PIN_0 | HAL_GPIO_PIN_1 | HAL_GPIO_PIN_2 | HAL_GPIO_PIN_3, &gpio_config);

#ifdef DIAG
	/* Configure diagnostic output pin on PA8 testpoint */
	gpio_config.mode            = HAL_GPIO_MODE_OUTPUT;
	gpio_config.speed           = HAL_GPIO_SPEED_FREQ_HIGH;
	gpio_config.pull            = HAL_GPIO_PULL_NO;
	gpio_config.output_type     = HAL_GPIO_OUTPUT_PUSHPULL;
	gpio_config.init_state      = HAL_GPIO_PIN_RESET;
	if (HAL_GPIO_Init(HAL_GPIOA, HAL_GPIO_PIN_8, &gpio_config) != HAL_OK)
	{
		return HAL_ERROR;
	}
#endif

	/* Configure DMA */
	if(HAL_DMA_Init(&hLPDMA1_CH0, HAL_LPDMA1_CH0) != HAL_OK)
	{
		return HAL_ERROR;
	}

	HAL_RCC_LPDMA1_EnableClock();

	hal_dma_direct_xfer_config_t xfer_cfg_adc1_dma;
	xfer_cfg_adc1_dma.request         = HAL_LPDMA1_REQUEST_ADC1;
	xfer_cfg_adc1_dma.direction       = HAL_DMA_DIRECTION_PERIPH_TO_MEMORY;
	xfer_cfg_adc1_dma.src_inc         = HAL_DMA_SRC_ADDR_FIXED;
	xfer_cfg_adc1_dma.dest_inc        = HAL_DMA_DEST_ADDR_INCREMENTED;
	xfer_cfg_adc1_dma.src_data_width  = HAL_DMA_SRC_DATA_WIDTH_HALFWORD;
	xfer_cfg_adc1_dma.dest_data_width = HAL_DMA_DEST_DATA_WIDTH_HALFWORD;
	xfer_cfg_adc1_dma.priority        = HAL_DMA_PRIORITY_LOW_WEIGHT_LOW;

	if(HAL_DMA_SetConfigPeriphLinkedListCircularXfer(&hLPDMA1_CH0, &DMA_Node_ADC1, &xfer_cfg_adc1_dma) != HAL_OK)
	{
		return HAL_ERROR;
	}

	/* Enable the interruption for LPDMA1_CH0 */
	HAL_CORTEX_NVIC_SetPriority(LPDMA1_CH0_IRQn, HAL_CORTEX_NVIC_PREEMP_PRIORITY_0, HAL_CORTEX_NVIC_SUB_PRIORITY_0);
	HAL_CORTEX_NVIC_EnableIRQ(LPDMA1_CH0_IRQn);

	/* Link DMA handle to ADC handle */
	HAL_ADC_REG_SetDMA(&hADC1, &hLPDMA1_CH0);
	
	/* register the DMA TC callback */
	if(HAL_ADC_RegisterDataTransferCpltCallback(&hADC1, ADC_TC_Callback) != HAL_OK)
	{
		return HAL_ERROR;
	}
	
	/* activate ADC */
	if(HAL_ADC_Start(&hADC1) != HAL_OK)
	{
		return HAL_ERROR;
	}

	/* Calibrate ADC */
	if(HAL_ADC_Calibrate(&hADC1) != HAL_OK)
	{
		return HAL_ERROR;
	}
	
	/* start conversions */
	if(HAL_ADC_REG_StartConv_DMA(&hADC1, (uint8_t *)adc_buffer, ADC_BUFSZ * sizeof(uint16_t)) != HAL_OK)
	{
		return HAL_ERROR;
	}
	
	adc_state = ADC_RUNNING;
	
	return HAL_OK;
}

/*
 * Pause / Play on running ADC to avoid sync issues caused by flash write
 */
hal_status_t ADC_PauseConv(uint8_t enable)
{
	hal_status_t status = HAL_OK;
	if(enable)
	{
		if(adc_state == ADC_RUNNING)
		{
			printf("Stopping ADC\n\r");
			if((status = HAL_ADC_REG_StopConv_DMA(&hADC1)) == HAL_OK)
			{
				LL_DMA_DisableChannel((DMA_Channel_TypeDef *)((uint32_t)hLPDMA1_CH0.instance));
				adc_state = ADC_PAUSED;
			}
		}
	}
	else
	{
		if(adc_state == ADC_PAUSED)
		{
			printf("Restarting ADC\n\r");
			if((status = HAL_ADC_REG_StartConv_DMA(&hADC1,
					(uint8_t *)adc_buffer,
			ADC_BUFSZ * sizeof(uint16_t))) == HAL_OK)
			{
				adc_state = ADC_RUNNING;
			}
		}
	}
	
	return status;
}

/*
 *
 */
int16_t ADC_GetChl(uint8_t chl)
{
	return adc_proc_buffer[chl];
}

/**
  * LPDMA1 Channel0 IRQ
  */
void LPDMA1_CH0_IRQHandler(void)
{
	/* Raise activity flag */
	DIAG_HIGH();

#ifndef SHORTHAL
	HAL_DMA_IRQHandler(&hLPDMA1_CH0);
#else
	/* Transfer complete interrupt */
	if(LPDMA1_CH0->CSR&DMA_CSR_TCF)
	{
		/* Clear the Interrupt flag */
		LPDMA1_CH0->CFCR = DMA_CFCR_TCF;
		
		/* grab data from previous DMA pass */
		memcpy(adc_proc_buffer, adc_buffer, ADC_BUFSZ*sizeof(int16_t));
	}
	
	/* clear any extraneous IRQs - usually HT that we don't use */
	if(LPDMA1_CH0->CSR&(DMA_CSR_HTF | DMA_CSR_DTEF | DMA_CSR_ULEF | DMA_CSR_USEF | DMA_CSR_SUSPF | DMA_CSR_TOF))
	{
		LPDMA1_CH0->CFCR = (DMA_CSR_HTF | DMA_CSR_DTEF | DMA_CSR_ULEF | DMA_CSR_USEF | DMA_CSR_SUSPF | DMA_CSR_TOF);
	}
#endif
	
	/* Lower activity flag */
	DIAG_LOW();
}

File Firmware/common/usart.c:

/*
 * usart.c - uart diag support for Cheep4
 * 04-09-26 E. Brombaugh
 */

#include "usart.h"

/* Handle for UART */
static hal_uart_handle_t hUSART1;

/* USART setup */
hal_uart_handle_t *usart_init(void)
{
  hal_uart_config_t uart_config;

  /* Basic configuration */
  if (HAL_UART_Init(&hUSART1, HAL_UART1) != HAL_OK)
  {
    return NULL;
  }

  HAL_RCC_USART1_EnableClock();

  if (HAL_RCC_USART1_SetKernelClkSource(HAL_RCC_USART1_CLK_SRC_PCLK2) != HAL_OK)
  {
    return NULL;
  }

  uart_config.baud_rate = 115200;
  uart_config.clock_prescaler = HAL_UART_PRESCALER_DIV1;
  uart_config.word_length = HAL_UART_WORD_LENGTH_8_BIT;
  uart_config.stop_bits = HAL_UART_STOP_BIT_1;
  uart_config.parity = HAL_UART_PARITY_NONE;
  uart_config.direction = HAL_UART_DIRECTION_TX_RX;
  uart_config.hw_flow_ctl = HAL_UART_HW_CONTROL_NONE;
  uart_config.oversampling = HAL_UART_OVERSAMPLING_16;
  uart_config.one_bit_sampling = HAL_UART_ONE_BIT_SAMPLE_DISABLE;

  if (HAL_UART_SetConfig(&hUSART1, &uart_config) != HAL_OK)
  {
    return NULL;
  }

  HAL_RCC_GPIOA_EnableClock();

  hal_gpio_config_t  gpio_config;

  /**
    USART1 GPIO Configuration

    [GPIO Pin] ------> [Signal Name]

       PA10    ------>   USART1_RX
    **/
  gpio_config.mode        = HAL_GPIO_MODE_ALTERNATE;
  gpio_config.output_type = HAL_GPIO_OUTPUT_PUSHPULL;
  gpio_config.pull        = HAL_GPIO_PULL_UP;
  gpio_config.speed       = HAL_GPIO_SPEED_FREQ_LOW;
  gpio_config.alternate   = HAL_GPIO_AF_7;
  HAL_GPIO_Init(HAL_GPIOA, HAL_GPIO_PIN_10, &gpio_config);

  /**
    USART1 GPIO Configuration

    [GPIO Pin] ------> [Signal Name]

       PA9     ------>   USART1_TX
    **/
  gpio_config.mode        = HAL_GPIO_MODE_ALTERNATE;
  gpio_config.output_type = HAL_GPIO_OUTPUT_PUSHPULL;
  gpio_config.pull        = HAL_GPIO_PULL_NO;
  gpio_config.speed       = HAL_GPIO_SPEED_FREQ_LOW;
  gpio_config.alternate   = HAL_GPIO_AF_7;
  HAL_GPIO_Init(HAL_GPIOA, HAL_GPIO_PIN_9, &gpio_config);
  
  
  /* enable TX/RX since HAL doesn't */
  USART1->CR1 |= (USART_CR1_TE | USART_CR1_RE | USART_CR1_UE);
  
  /* wait for ACK */
  while(!(USART1->ISR & (USART_ISR_TEACK | USART_ISR_REACK))){}

  return &hUSART1;
}

/*
 * output for tiny printf
 */
void usart_putc(void* p, char c)
{
	while(!(USART1->ISR & USART_ISR_TC))
	{
	}
	USART1->TDR = c;
}

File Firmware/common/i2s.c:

/*
 * i2s.c - cheep4 STM32C542 i2s setup
 * 04-14-2026 E. Brombaugh
 */

#include <string.h>
#include "i2s.h"
#include "audio.h"
#include "printf.h"
#include "cyclesleep.h"

/* uncomment to shortcut HAL callbacks */
#define SHORTHAL

/* uncomment to enable IRQ diag on TP3 / PA8 pin */
#define DIAG

#ifdef DIAG
#define DIAG_LOW()	(GPIOA->BSRR=(HAL_GPIO_PIN_8<<16))
#define DIAG_HIGH()	(GPIOA->BSRR=HAL_GPIO_PIN_8)
#else
#define DIAG_LOW()
#define DIAG_HIGH()
#endif

static hal_i2s_handle_t hSPI2;
static hal_dma_node_t DMA_Node_SPI2_TX;
static hal_dma_handle_t hLPDMA1_CH1;

int16_t i2s_buffer[I2S_BUFSZ];

/*
 * I2S DMA HT callback
 */
void I2S_HT_Callback(hal_i2s_handle_t *hi2s)
{
#ifndef SHORTHAL
	/* refill 1st half */
	audio_gen(&i2s_buffer[0], I2S_BUFSZ/2);
#endif
}

/*
 * I2S DMA TC callback
 */
void I2S_TC_Callback(hal_i2s_handle_t *hi2s)
{
#ifndef SHORTHAL
	/* refill 2nd half */
	audio_gen(&i2s_buffer[I2S_BUFSZ/2], I2S_BUFSZ/2);
#endif
}

/*
 * Initialize the I2S transmit port
 */
hal_status_t I2S_Init(void)
{
	hal_i2s_master_config_t i2s_config;

	if(HAL_I2S_Init(&hSPI2, HAL_I2S2) != HAL_OK)
	{
		printf("HAL_I2S_Init() failed\n\r");
		return HAL_ERROR;
	}

	HAL_RCC_SPI2_EnableClock();

	if(HAL_RCC_SPI2_SetKernelClkSource(HAL_RCC_SPI2_CLK_SRC_PCLK1) != HAL_OK)
	{
		printf("HAL_RCC_SPI2_SetKernelClkSource() failed\n\r");
		return HAL_ERROR;
	}

	i2s_config.mode = HAL_I2S_MODE_MASTER_TX;
	i2s_config.standard = HAL_I2S_STANDARD_PHILIPS;
	i2s_config.data_format = HAL_I2S_DATA_FORMAT_16_BIT;
	i2s_config.audio_frequency = HAL_I2S_MASTER_AUDIO_FREQ_96_KHZ;
	i2s_config.clock_polarity = HAL_I2S_CLOCK_POLARITY_LOW;
	i2s_config.bit_order = HAL_I2S_MSB_FIRST;
	if(HAL_I2S_MASTER_SetConfig(&hSPI2, &i2s_config) != HAL_OK)
	{
		printf("HAL_I2S_MASTER_SetConfig() failed\n\r");
		return HAL_ERROR;
	}

	if(HAL_I2S_SetFifoThreshold(&hSPI2, HAL_I2S_FIFO_THRESHOLD_1_DATA) != HAL_OK)
	{
		printf("HAL_I2S_SetFifoThreshold() failed\n\r");
		return HAL_ERROR;
	}

	HAL_RCC_GPIOB_EnableClock();

	hal_gpio_config_t  gpio_config;

	/**
		SPI2 GPIO Configuration

		[GPIO Pin] ------> [Signal Name]

		PB12    ------>   I2S2_WS
		PB13    ------>   I2S2_CK
		PB15    ------>   I2S2_SDO
	**/
	gpio_config.mode        = HAL_GPIO_MODE_ALTERNATE;
	gpio_config.output_type = HAL_GPIO_OUTPUT_PUSHPULL;
	gpio_config.pull        = HAL_GPIO_PULL_NO;
	gpio_config.speed       = HAL_GPIO_SPEED_FREQ_LOW;
	gpio_config.alternate   = HAL_GPIO_AF_5;
	HAL_GPIO_Init(HAL_GPIOB, HAL_GPIO_PIN_13 | HAL_GPIO_PIN_12 | HAL_GPIO_PIN_15, &gpio_config);

#ifdef DIAG
	/* Configure diagnostic output pin on PA8 testpoint */
	HAL_RCC_GPIOA_EnableClock();
	gpio_config.mode            = HAL_GPIO_MODE_OUTPUT;
	gpio_config.speed           = HAL_GPIO_SPEED_FREQ_HIGH;
	gpio_config.pull            = HAL_GPIO_PULL_NO;
	gpio_config.output_type     = HAL_GPIO_OUTPUT_PUSHPULL;
	gpio_config.init_state      = HAL_GPIO_PIN_RESET;
	if (HAL_GPIO_Init(HAL_GPIOA, HAL_GPIO_PIN_8, &gpio_config) != HAL_OK)
	{
		printf("HAL_GPIO_Init() failed\n\r");
		return HAL_ERROR;
	}
#endif
	/* Configure the DMA TX */
	if(HAL_DMA_Init(&hLPDMA1_CH1, HAL_LPDMA1_CH1) != HAL_OK)
	{
		printf("HAL_DMA_Init() failed\n\r");
		return HAL_ERROR;
	}

	HAL_RCC_LPDMA1_EnableClock();

	hal_dma_direct_xfer_config_t xfer_cfg_spi2_tx_dma;
	xfer_cfg_spi2_tx_dma.request         = HAL_LPDMA1_REQUEST_SPI2_TX;
	xfer_cfg_spi2_tx_dma.direction       = HAL_DMA_DIRECTION_MEMORY_TO_PERIPH;
	xfer_cfg_spi2_tx_dma.src_inc         = HAL_DMA_SRC_ADDR_INCREMENTED;
	xfer_cfg_spi2_tx_dma.dest_inc        = HAL_DMA_DEST_ADDR_FIXED;
	xfer_cfg_spi2_tx_dma.src_data_width  = HAL_DMA_SRC_DATA_WIDTH_HALFWORD;
	xfer_cfg_spi2_tx_dma.dest_data_width = HAL_DMA_DEST_DATA_WIDTH_HALFWORD;
	xfer_cfg_spi2_tx_dma.priority        = HAL_DMA_PRIORITY_HIGH;
	if(HAL_DMA_SetConfigPeriphLinkedListCircularXfer(&hLPDMA1_CH1, &DMA_Node_SPI2_TX, &xfer_cfg_spi2_tx_dma) != HAL_OK)
	{
		printf("HAL_DMA_SetConfigPeriphLinkedListCircularXfer() failed\n\r");
		return HAL_ERROR;
	}

	/* Enable the interruption for LPDMA1_CH1 */
	HAL_CORTEX_NVIC_SetPriority(LPDMA1_CH1_IRQn, HAL_CORTEX_NVIC_PREEMP_PRIORITY_0, HAL_CORTEX_NVIC_SUB_PRIORITY_0);
	HAL_CORTEX_NVIC_EnableIRQ(LPDMA1_CH1_IRQn);

	/* Link the Transmit DMA handle to the I2S handle */
	if(HAL_I2S_SetTxDMA(&hSPI2, &hLPDMA1_CH1) != HAL_OK)
	{
		printf("HAL_I2S_SetTxDMA() failed\n\r");
		return HAL_ERROR;
	}

	if(HAL_RCC_SPI2_SetKernelClkSource(HAL_RCC_SPI2_CLK_SRC_PCLK1) != HAL_OK)
	{
		printf("HAL_RCC_SPI2_SetKernelClkSource() failed\n\r");
		return HAL_ERROR;
	}

	/* register the DMA HT callback */
	if(HAL_I2S_RegisterTxHalfCpltCallback(&hSPI2, I2S_HT_Callback)!= HAL_OK)
	{
		printf("HAL_I2S_RegisterTxHalfCpltCallback() failed\n\r");
		return HAL_ERROR;
	}
	
	/* register the DMA TC callback */
	if(HAL_I2S_RegisterTxCpltCallback(&hSPI2, I2S_TC_Callback)!= HAL_OK)
	{
		printf("HAL_I2S_RegisterTxCpltCallback() failed\n\r");
		return HAL_ERROR;
	}
	
	/* Start transmitting */
	if(HAL_I2S_Transmit_DMA(&hSPI2, i2s_buffer, I2S_BUFSZ) != HAL_OK)
	{
		printf("HAL_I2S_Transmit_DMA() failed\n\r");
		return HAL_ERROR;
	}
	
	return HAL_OK;
}

/*
 * Compute actual sampling frequency
 */
int32_t I2S_GetFsamp(void)
{
	int32_t calc_Fsamp;

#if 0	
	calc_Fsamp = HAL_I2S_MASTER_GetAudioFrequency(&hSPI2);
#else
	uint32_t cfgr = ((SPI_TypeDef*)((uint32_t)(&hSPI2)->instance))->I2SCFGR;
	int32_t ODD = (cfgr & SPI_I2SCFGR_ODD) >> SPI_I2SCFGR_ODD_Pos;
	int32_t CHLEN = (cfgr & SPI_I2SCFGR_CHLEN) >> SPI_I2SCFGR_CHLEN_Pos;
	int32_t I2SDIV = (cfgr & SPI_I2SCFGR_I2SDIV ) >> SPI_I2SCFGR_I2SDIV_Pos;
	calc_Fsamp = HAL_RCC_GetSYSCLKFreq()/(32 * (CHLEN + 1) * ((2 * I2SDIV) + ODD));
#endif
	
	return calc_Fsamp;
}


/**
  * LPDMA1 Channel0 IRQ
  */
void LPDMA1_CH1_IRQHandler(void)
{
	/* Raise activity flag */
	DIAG_HIGH();
	
	/* start cpu load est */
	start_meas();

#ifndef SHORTHAL
	HAL_DMA_IRQHandler(&hLPDMA1_CH1);
#else
	/* Half-transfer interrupt */
	if(LPDMA1_CH1->CSR&DMA_CSR_HTF)
	{
		/* Clear the Interrupt flag */
		LPDMA1_CH1->CFCR = DMA_CFCR_HTF;
		
		/* refill 1st half */
		audio_gen(&i2s_buffer[0], I2S_BUFSZ/2);
	}
	
	/* Transfer complete interrupt */
	if(LPDMA1_CH1->CSR&DMA_CSR_TCF)
	{
		/* Clear the Interrupt flag */
		LPDMA1_CH1->CFCR = DMA_CFCR_TCF;
		
		/* refill 2nd half */
		audio_gen(&i2s_buffer[I2S_BUFSZ/2], I2S_BUFSZ/2);
	}
	
	/* clear any extraneous IRQs - generally there are none */
	if(LPDMA1_CH0->CSR&(DMA_CSR_DTEF | DMA_CSR_ULEF | DMA_CSR_USEF | DMA_CSR_SUSPF | DMA_CSR_TOF))
	{
		LPDMA1_CH0->CFCR = (DMA_CSR_DTEF | DMA_CSR_ULEF | DMA_CSR_USEF | DMA_CSR_SUSPF | DMA_CSR_TOF);
	}
#endif
	
	/* finish cpu load est */
	end_meas();

	/* Lower activity flag */
	DIAG_LOW();
}

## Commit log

2026-04-22 Inital checkin of Cheep4 project
2026-04-27 Adding latest updates for osc functionality & general HW support.
2026-04-28 Updated documentation
2026-04-28 Updated with more detail, links.

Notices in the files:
Hardware/cheep4/cheep4.kicad_pcb:
(c) 2026
parts and their libraries:
Copyright 2016 Accelerated Designs. All rights reserved.
